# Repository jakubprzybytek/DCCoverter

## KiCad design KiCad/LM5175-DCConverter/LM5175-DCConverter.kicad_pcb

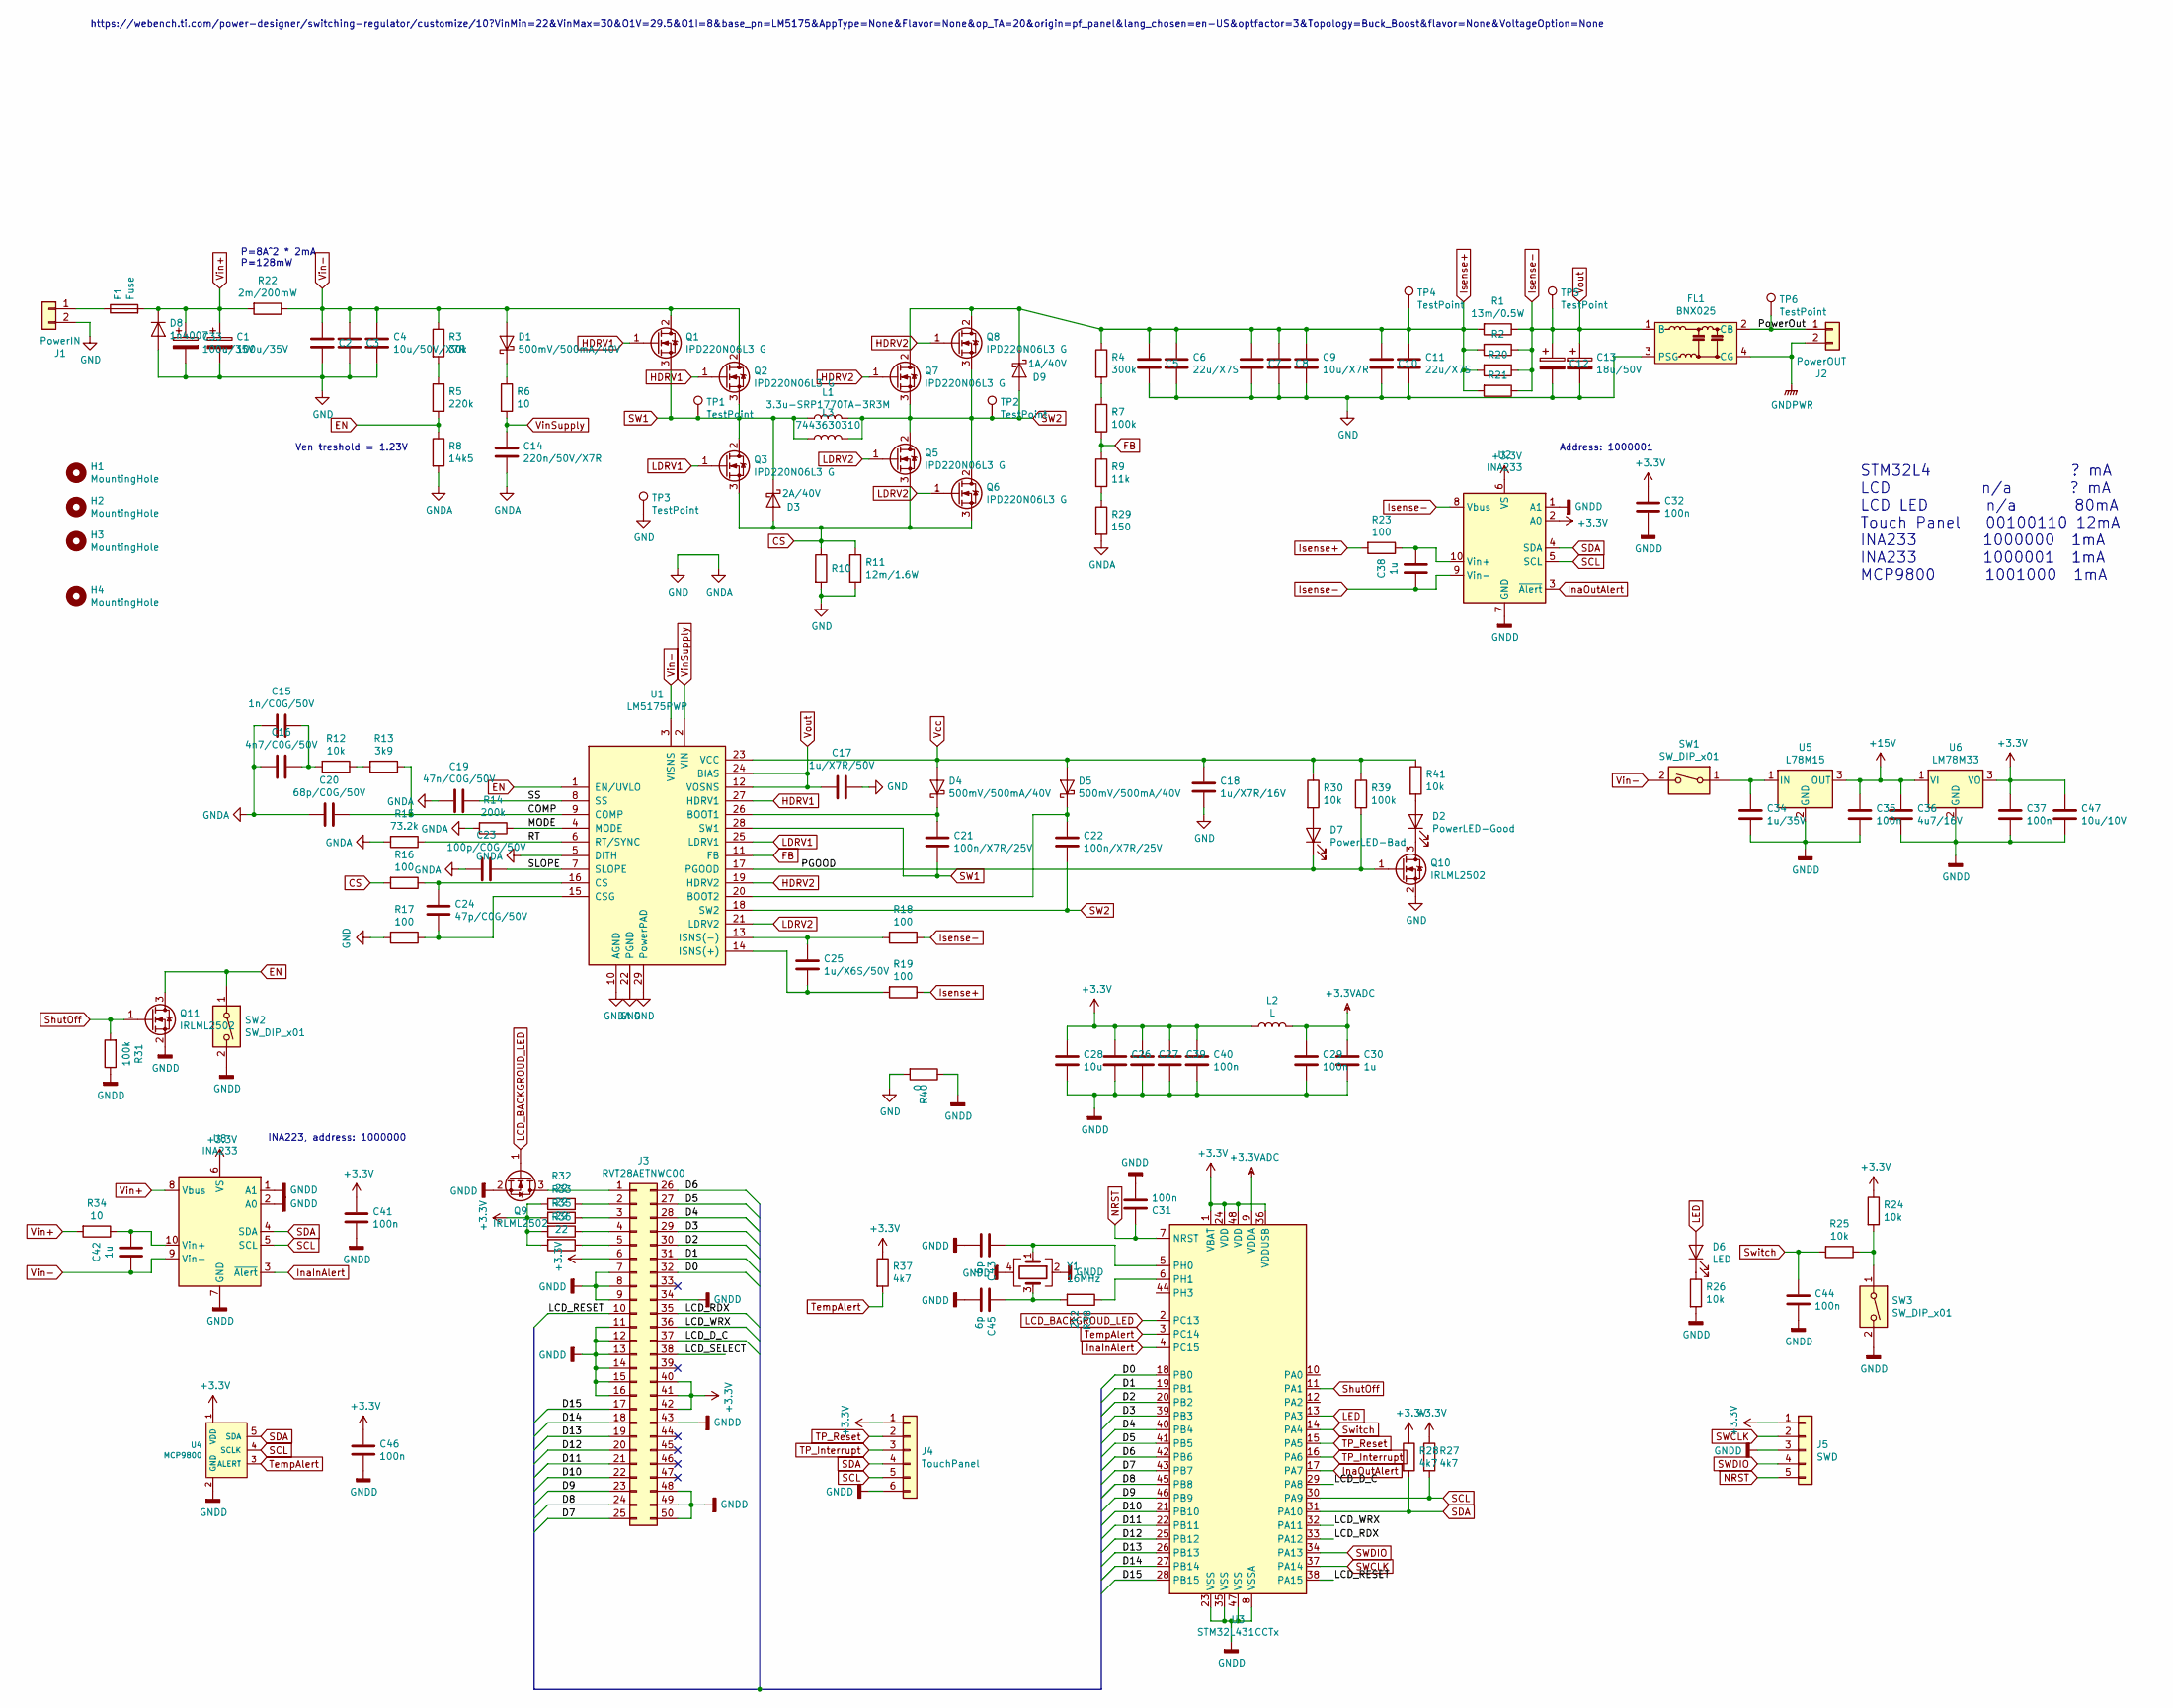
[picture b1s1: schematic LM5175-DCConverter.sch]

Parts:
C1, C33: 100u/35V; C_Elec_8x6.2
C2, C3, C4: 10u/50V/X7R; C_1210_3225Metric
C5, C6, C10, C11: 22u/X7S; C_2220_5650Metric
C7, C8, C9: 10u/X7R; C_2220_5650Metric
C12, C13: 18u/50V; C_Elec_6.3x5.8
C14: 220n/50V/X7R; C_0805_2012Metric
C15: 1n/C0G/50V; C_0805_2012Metric
C16: 4n7/C0G/50V; C_0805_2012Metric
C17: 1u/X7R/50V; C_0805_2012Metric
C18: 1u/X7R/16V; C_0805_2012Metric
C19: 47n/C0G/50V; C_0805_2012Metric
C20: 68p/C0G/50V; C_0805_2012Metric
C21, C22: 100n/X7R/25V; C_0805_2012Metric
C23: 100p/C0G/50V; C_0805_2012Metric
C24: 47p/C0G/50V; C_0805_2012Metric
C25: 1u/X6S/50V; C_0805_2012Metric
C26, C27, C29, C31, C32, C35, C37, C39, C40, C41, C44, C46: 100n; C_0603_1608Metric
C28: 10u; C_0805_2012Metric
C30, C38, C42: 1u; C_0805_2012Metric
C34: 1u/35V; C_1206_3216Metric
C36: 4u7/16V; C_1206_3216Metric
C43, C45: 6p; C_0805_2012Metric
C47: 10u/10V; C_1206_3216Metric
D1, D4, D5: 500mV/500mA/40V; D_SMA
D2: PowerLED-Good; LED_0805_2012Metric
D3: 2A/40V; D_SMB
D6: LED; LED_0805_2012Metric
D7: PowerLED-Bad; LED_0805_2012Metric
D8: 1n4007; D_MELF
D9: 1A/40V; D_SMB
F1: Fuse; Fuseholder5x20_horiz_open_big
FL1: BNX025; Filter_Murata_BNX005
H1, H2, H3, H4: MountingHole; MountingHole_3.2mm_M3
J1: PowerIN; XT60PW-M
J2: PowerOUT; XT60PW-M
J3: RVT28AETNWC00; Hirose_FH12-50S-0.5SH_1x50-1MP_P0.50mm_Horizontal
J4: TouchPanel; TE_0-1734839-6_1x06-1MP_P0.5mm_Horizontal
J5: SWD; PinHeader_1x05_P2.54mm_Horizontal
L1: 3.3u-SRP1770TA-3R3M; L_Bourns_SRP1770TA
L2: L; L_0805_2012Metric
L3: 7443630310; L_Wuerth_WE-HCF
Q1, Q2, Q3, Q5, Q6, Q7, Q8: IPD220N06L3 G; TO-252-2
Q9, Q10, Q11: IRLML2502; SOT-23
R1, R2, R20, R21: 13m/0.5W; R_1206_3216Metric
R3: 30k; R_0805_2012Metric
R4: 300k; R_0805_2012Metric
R5: 220k; R_0805_2012Metric
R6: 10; R_1206_3216Metric
R7, R31, R39: 100k; R_0805_2012Metric
R8: 14k5; R_0805_2012Metric
R9: 11k; R_0805_2012Metric
R10, R11: 12m/1.6W; R_2512_6332Metric
R12, R26, R30, R41: 10k; R_0805_2012Metric
R13: 3k9; R_0805_2012Metric
R14: 200k; R_0805_2012Metric
R15: 73.2k; R_0805_2012Metric
R16, R17, R18, R19, R23: 100; R_0805_2012Metric
R22: 2m/200mW; R_2512_6332Metric
R24, R25: 10k; R_0603_1608Metric
R27, R28, R37: 4k7; R_0805_2012Metric
R29: 150; R_0805_2012Metric
R32, R33, R35, R36: 22; R_0805_2012Metric
R34: 10; R_0805_2012Metric
R38: 2k2; R_0805_2012Metric
R40: 0; SolderJumper-2_P1.3mm_Bridged2Bar_Pad1.0x1.5mm
SW1, SW2: SW_DIP_x01; JST_PH_S2B-PH-K_1x02_P2.00mm_Horizontal
SW3: SW_DIP_x01; SW_SPST_B3S-1000
TP1, TP2, TP3, TP4, TP5, TP6: TestPoint; TestPoint_THTPad_D1.0mm_Drill0.5mm
U1: LM5175PWP; HTSSOP-28-1EP_4.4x9.7mm_P0.65mm_EP3.4x9.5mm_ThermalVias
U2, U8: INA233; VSSOP-10_3x3mm_P0.5mm
U3: STM32L431CCTx; LQFP-48_7x7mm_P0.5mm
U4: MCP9800; SOT-23-5
U5: L78M15; TO-252-2
U6: LM78M33; TO-252-2
Y1: 16MHz; Crystal_SMD_Abracon_ABM3B-4Pin_5.0x3.2mm

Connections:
+3.3VADC: C29.1, C30.1, L2.2, U3.9 (VDDA)
+3V3: C26.1, C27.1, C28.1, C32.1, C37.1, C39.1, C40.1, C41.1, C46.1, C47.1, J3.6, J3.40, J3.41, J3.42, J4.1, J5.1, L2.1, R24.1, R27.1, R28.1, R32.2, R33.2, R35.2, R36.2, R37.1, U2.2 (A0), U2.6 (VS), U3.1 (VBAT), U3.24 (VDD), U3.36 (VDDUSB), U3.48 (VDD), U4.1 (VDD), U6.3 (VO), U8.6 (VS)
+15V: C35.1, C36.1, U5.3 (OUT), U6.1 (VI)
/COMP: C20.2, R13.1, U1.9 (COMP)
/D0: J3.32, U3.18 (PB0)
/D1: J3.31, U3.19 (PB1)
/D2: J3.30, U3.20 (PB2)
/D3: J3.29, U3.39 (PB3)
/D4: J3.28, U3.40 (PB4)
/D5: J3.27, U3.41 (PB5)
/D6: J3.26, U3.42 (PB6)
/D7: J3.25, U3.43 (PB7)
/D8: J3.24, U3.45 (PB8)
/D9: J3.23, U3.46 (PB9)
/D10: J3.22, U3.21 (PB10)
/D11: J3.21, U3.22 (PB11)
/D12: J3.20, U3.25 (PB12)
/D13: J3.19, U3.26 (PB13)
/D14: J3.18, U3.27 (PB14)
/D15: J3.17, U3.28 (PB15)
/LCD_D_C: J3.37, U3.29 (PA8)
/LCD_RDX: J3.35, U3.33 (PA12)
/LCD_RESET: J3.10, U3.38 (PA15)
/LCD_SELECT: J3.38
/LCD_WRX: J3.36, U3.32 (PA11)
/MODE: R14.1, U1.4 (MODE)
/PGOOD: D7.1 (K), Q10.1 (G), R39.2, U1.17 (PGOOD)
/PowerOut: FL1.2 (CB), J2.1, TP6.1
/RT: R15.1, U1.6 (RT/SYNC)
/SLOPE: C23.2, U1.7 (SLOPE)
/SS: C19.2, U1.8 (SS)
CS: D3.2 (A), Q3.3 (S), Q5.3 (S), Q6.3 (S), R10.1, R11.1, R16.2
EN: Q11.3 (D), R5.2, R8.1, SW2.1, U1.1 (EN/UVLO)
FB: R7.2, R9.1, U1.11 (FB)
GND: C1.2, C2.2, C3.2, C4.2, C5.2, C6.2, C7.2, C8.2, C9.2, C10.2, C11.2, C12.2, C13.2, C14.2, C15.1, C16.1, C17.1, C18.2, C19.1, C20.1, C23.1, C33.2, D8.2 (A), FL1.3 (PSG), J1.2, Q10.2 (S), R8.2, R10.2, R11.2, R14.2, R15.2, R17.2, R29.2, R40.2, TP3.1, U1.5 (DITH), U1.10 (AGND), U1.22 (PGND), U1.29 (PowerPAD)
GNDD: C26.2, C27.2, C28.2, C29.2, C30.2, C31.2, C32.2, C34.2, C35.2, C36.2, C37.2, C39.2, C40.2, C41.2, C43.2, C44.2, C45.2, C46.2, C47.2, J3.7, J3.8, J3.9, J3.11, J3.12, J3.13, J3.14, J3.15, J3.16, J3.34, J3.43, J3.48, J3.49, J3.50, J4.6, J5.3, Q9.2 (S), Q11.2 (S), R26.2, R31.1, R40.1, SW2.2, SW3.2, U2.1 (A1), U2.7 (GND), U3.8 (VSSA), U3.23 (VSS), U3.35 (VSS), U3.47 (VSS), U4.2 (GND), U5.2 (GND), U6.2 (GND), U8.1 (A1), U8.2 (A0), U8.7 (GND), Y1.2, Y1.4
GNDPWR: FL1.4 (CG), J2.2
HDRV1: Q1.1 (G), Q2.1 (G), U1.27 (HDRV1)
HDRV2: Q7.1 (G), Q8.1 (G), U1.19 (HDRV2)
InaInAlert: U3.4 (PC15), U8.3 (~Alert~)
InaOutAlert: U2.3 (~Alert~), U3.17 (PA7)
Isense+: C5.1, C6.1, C7.1, C8.1, C9.1, C10.1, C11.1, D9.1 (K), Q7.2 (D), Q8.2 (D), R1.2, R2.2, R4.1, R19.1, R20.2, R21.2, R23.2, TP4.1
Isense-: C12.1, C13.1, C17.2, C38.2, FL1.1 (B), R1.1, R2.1, R18.1, R20.1, R21.1, TP5.1, U1.12 (VOSNS), U1.24 (BIAS), U2.8 (Vbus), U2.9 (Vin-)
LCD_BACKGROUD_LED: Q9.1 (G), U3.2 (PC13)
LDRV1: Q3.1 (G), U1.25 (LDRV1)
LDRV2: Q5.1 (G), Q6.1 (G), U1.21 (LDRV2)
LED: D6.2 (A), U3.13 (PA3)
NRST: C31.1, J5.5, U3.7 (NRST)
unnamed: C15.2, C16.2, R12.2
unnamed: C21.1, D4.1 (K), U1.26 (BOOT1)
unnamed: C22.1, D5.1 (K), U1.20 (BOOT2)
unnamed: C24.1, R16.1, U1.16 (CS)
unnamed: C24.2, R17.1, U1.15 (CSG)
unnamed: C25.1, R18.2, U1.13 (ISNS(-))
unnamed: C25.2, R19.2, U1.14 (ISNS(+))
unnamed: C34.1, SW1.1, U5.1 (IN)
unnamed: C38.1, R23.1, U2.10 (Vin+)
unnamed: C42.1, R34.1, U8.10 (Vin+)
unnamed: C43.1, U3.5 (PH0), Y1.1
unnamed: C45.1, R38.2, Y1.3
unnamed: D1.1 (K), R6.1
unnamed: D2.1 (K), Q10.3 (D)
unnamed: D2.2 (A), R41.2
unnamed: D6.1 (K), R26.1
unnamed: D7.2 (A), R30.2
unnamed: F1.1, J1.1
unnamed: J3.1, Q9.3 (D)
unnamed: J3.2, R32.1
unnamed: J3.3, R33.1
unnamed: J3.4, R35.1
unnamed: J3.5, R36.1
unnamed: R3.2, R5.1
unnamed: R4.2, R7.1
unnamed: R12.1, R13.2
unnamed: R24.2, R25.1, SW3.1
unnamed: R9.2, R29.1
unnamed: R38.1, U3.6 (PH1)
SCL: J4.5, R27.2, U2.5 (SCL), U3.30 (PA9), U4.4 (SCLK), U8.5 (SCL)
SDA: J4.4, R28.2, U2.4 (SDA), U3.31 (PA10), U4.5 (SDA), U8.4 (SDA)
SW1: C21.2, D3.1 (K), L1.1, L3.1, Q1.3 (S), Q2.3 (S), Q3.2 (D), TP1.1, U1.28 (SW1)
SW2: C22.2, D9.2 (A), L1.2, L3.2, Q5.2 (D), Q6.2 (D), Q7.3 (S), Q8.3 (S), TP2.1, U1.18 (SW2)
SWCLK: J5.2, U3.37 (PA14)
SWDIO: J5.4, U3.34 (PA13)
ShutOff: Q11.1 (G), R31.2, U3.11 (PA1)
Switch: C44.1, R25.2, U3.14 (PA4)
TP_Interrupt: J4.3, U3.16 (PA6)
TP_Reset: J4.2, U3.15 (PA5)
TempAlert: R37.2, U3.3 (PC14), U4.3 (ALERT)
Vcc: C18.1, D4.2 (A), D5.2 (A), R30.1, R39.1, R41.1, U1.23 (VCC)
Vin+: C1.1, C33.1, D8.1 (K), F1.2, R22.2, R34.2, U8.8 (Vbus)
Vin-: C2.1, C3.1, C4.1, C42.2, D1.2 (A), Q1.2 (D), Q2.2 (D), R3.1, R22.1, SW1.2, U1.3 (VISNS), U8.9 (Vin-)
VinSupply: C14.1, R6.2, U1.2 (VIN)

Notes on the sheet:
Address: 1000001
STM32L4 ? mA LCD n/a ? mA LCD LED n/a 80mA Touch Panel 00100110 12mA INA233 1000000 1mA INA233 1000001 1mA MCP9800 1001000 1mA
INA223, address: 1000000
https://webench.ti.com/power-designer/switching-regulator/customize/10?VinMin=22&VinMax=30&O1V=29.5&O1I=8&base_pn=LM5175&AppType=None&Flavor=None&op_TA=20&origin=pf_panel&lang_chosen=en-US&optfactor=3&Topology=Buck_Boost&flavor=None&VoltageOption=None
Ven treshold = 1.23V
P=8A^2 * 2mA P=128mW

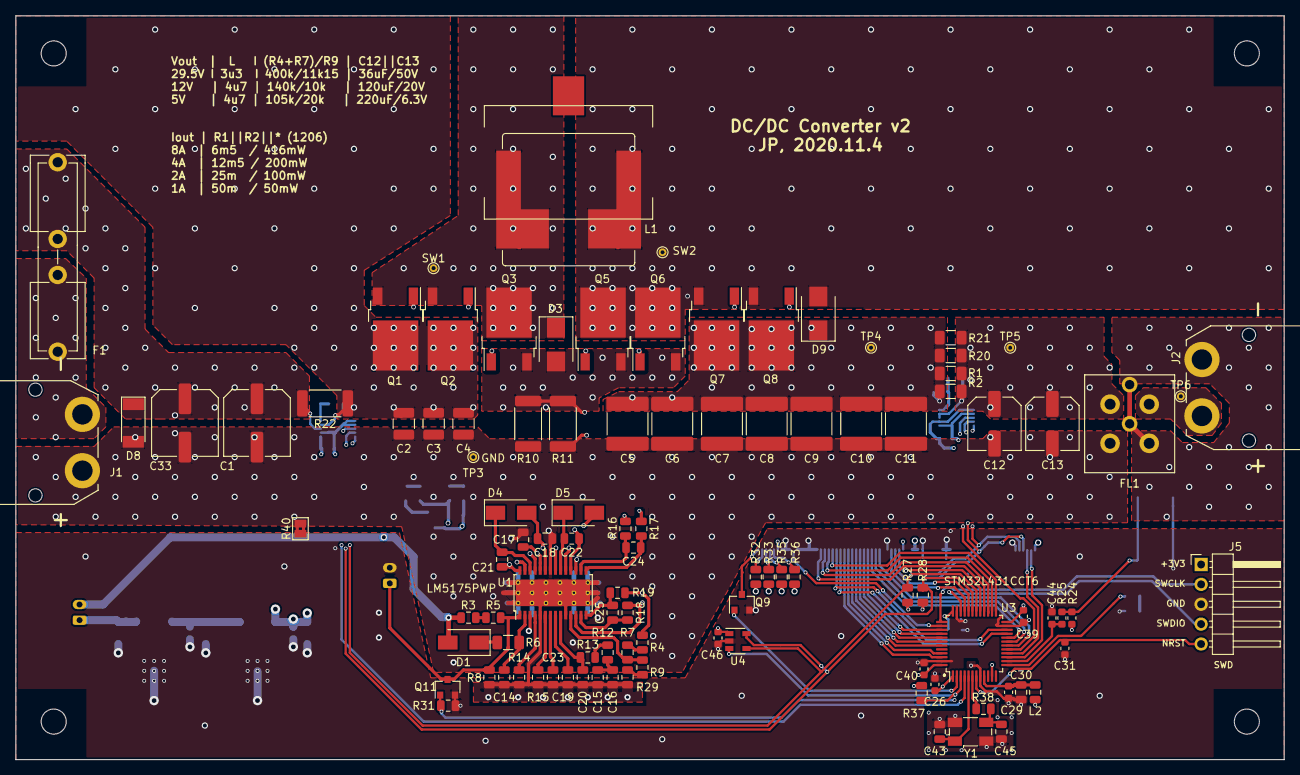
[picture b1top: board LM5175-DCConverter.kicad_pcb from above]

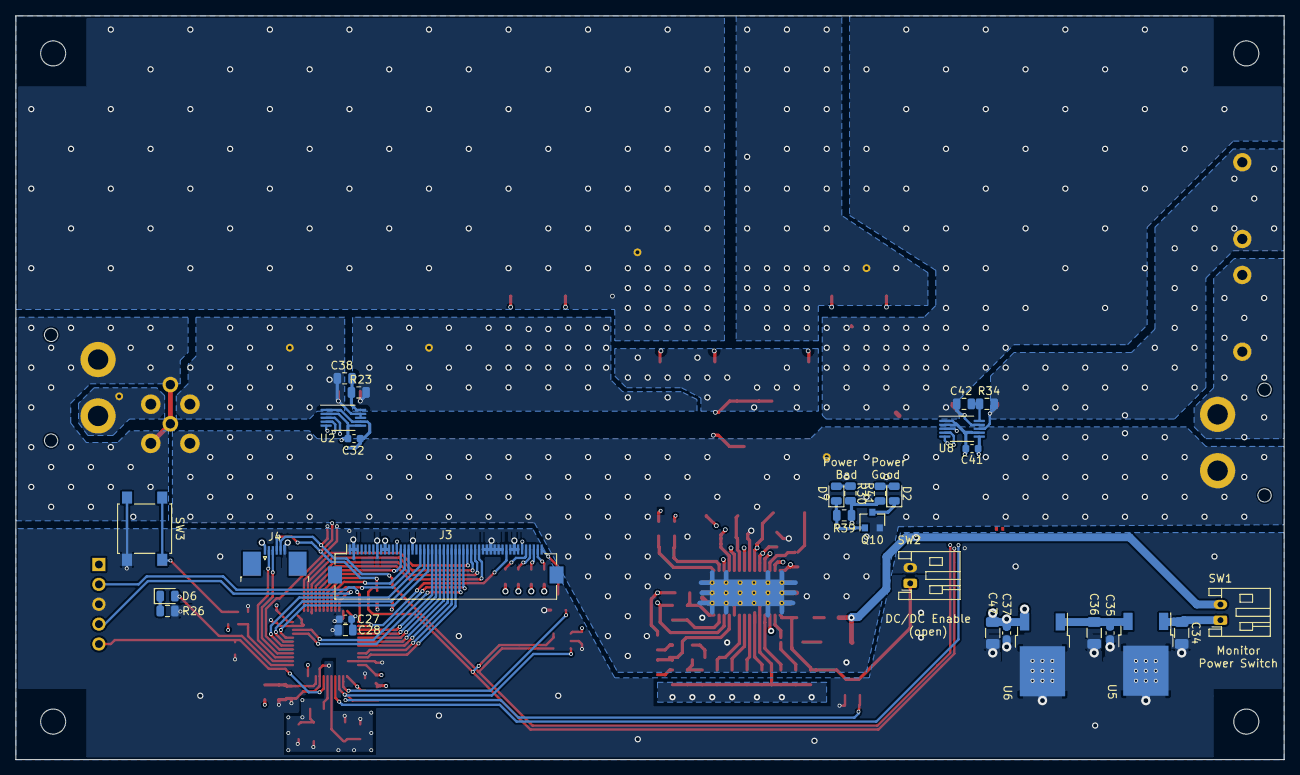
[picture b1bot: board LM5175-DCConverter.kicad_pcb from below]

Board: 4 copper layers, 162.0 x 95.0 mm, 138 parts (30 on the bottom side), 91 nets.

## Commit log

2020-01-30 Init commit
2020-02-02 stm32 added
2020-02-09 MOre PCB work
2020-02-14 Most of the PCB done
2020-07-19 Save before stm32 change
2020-09-28 First fixes after soldering
2020-10-31 Post assembling notes
2020-11-01 Work on pcb v2
2020-11-04 Last fixes for v2
